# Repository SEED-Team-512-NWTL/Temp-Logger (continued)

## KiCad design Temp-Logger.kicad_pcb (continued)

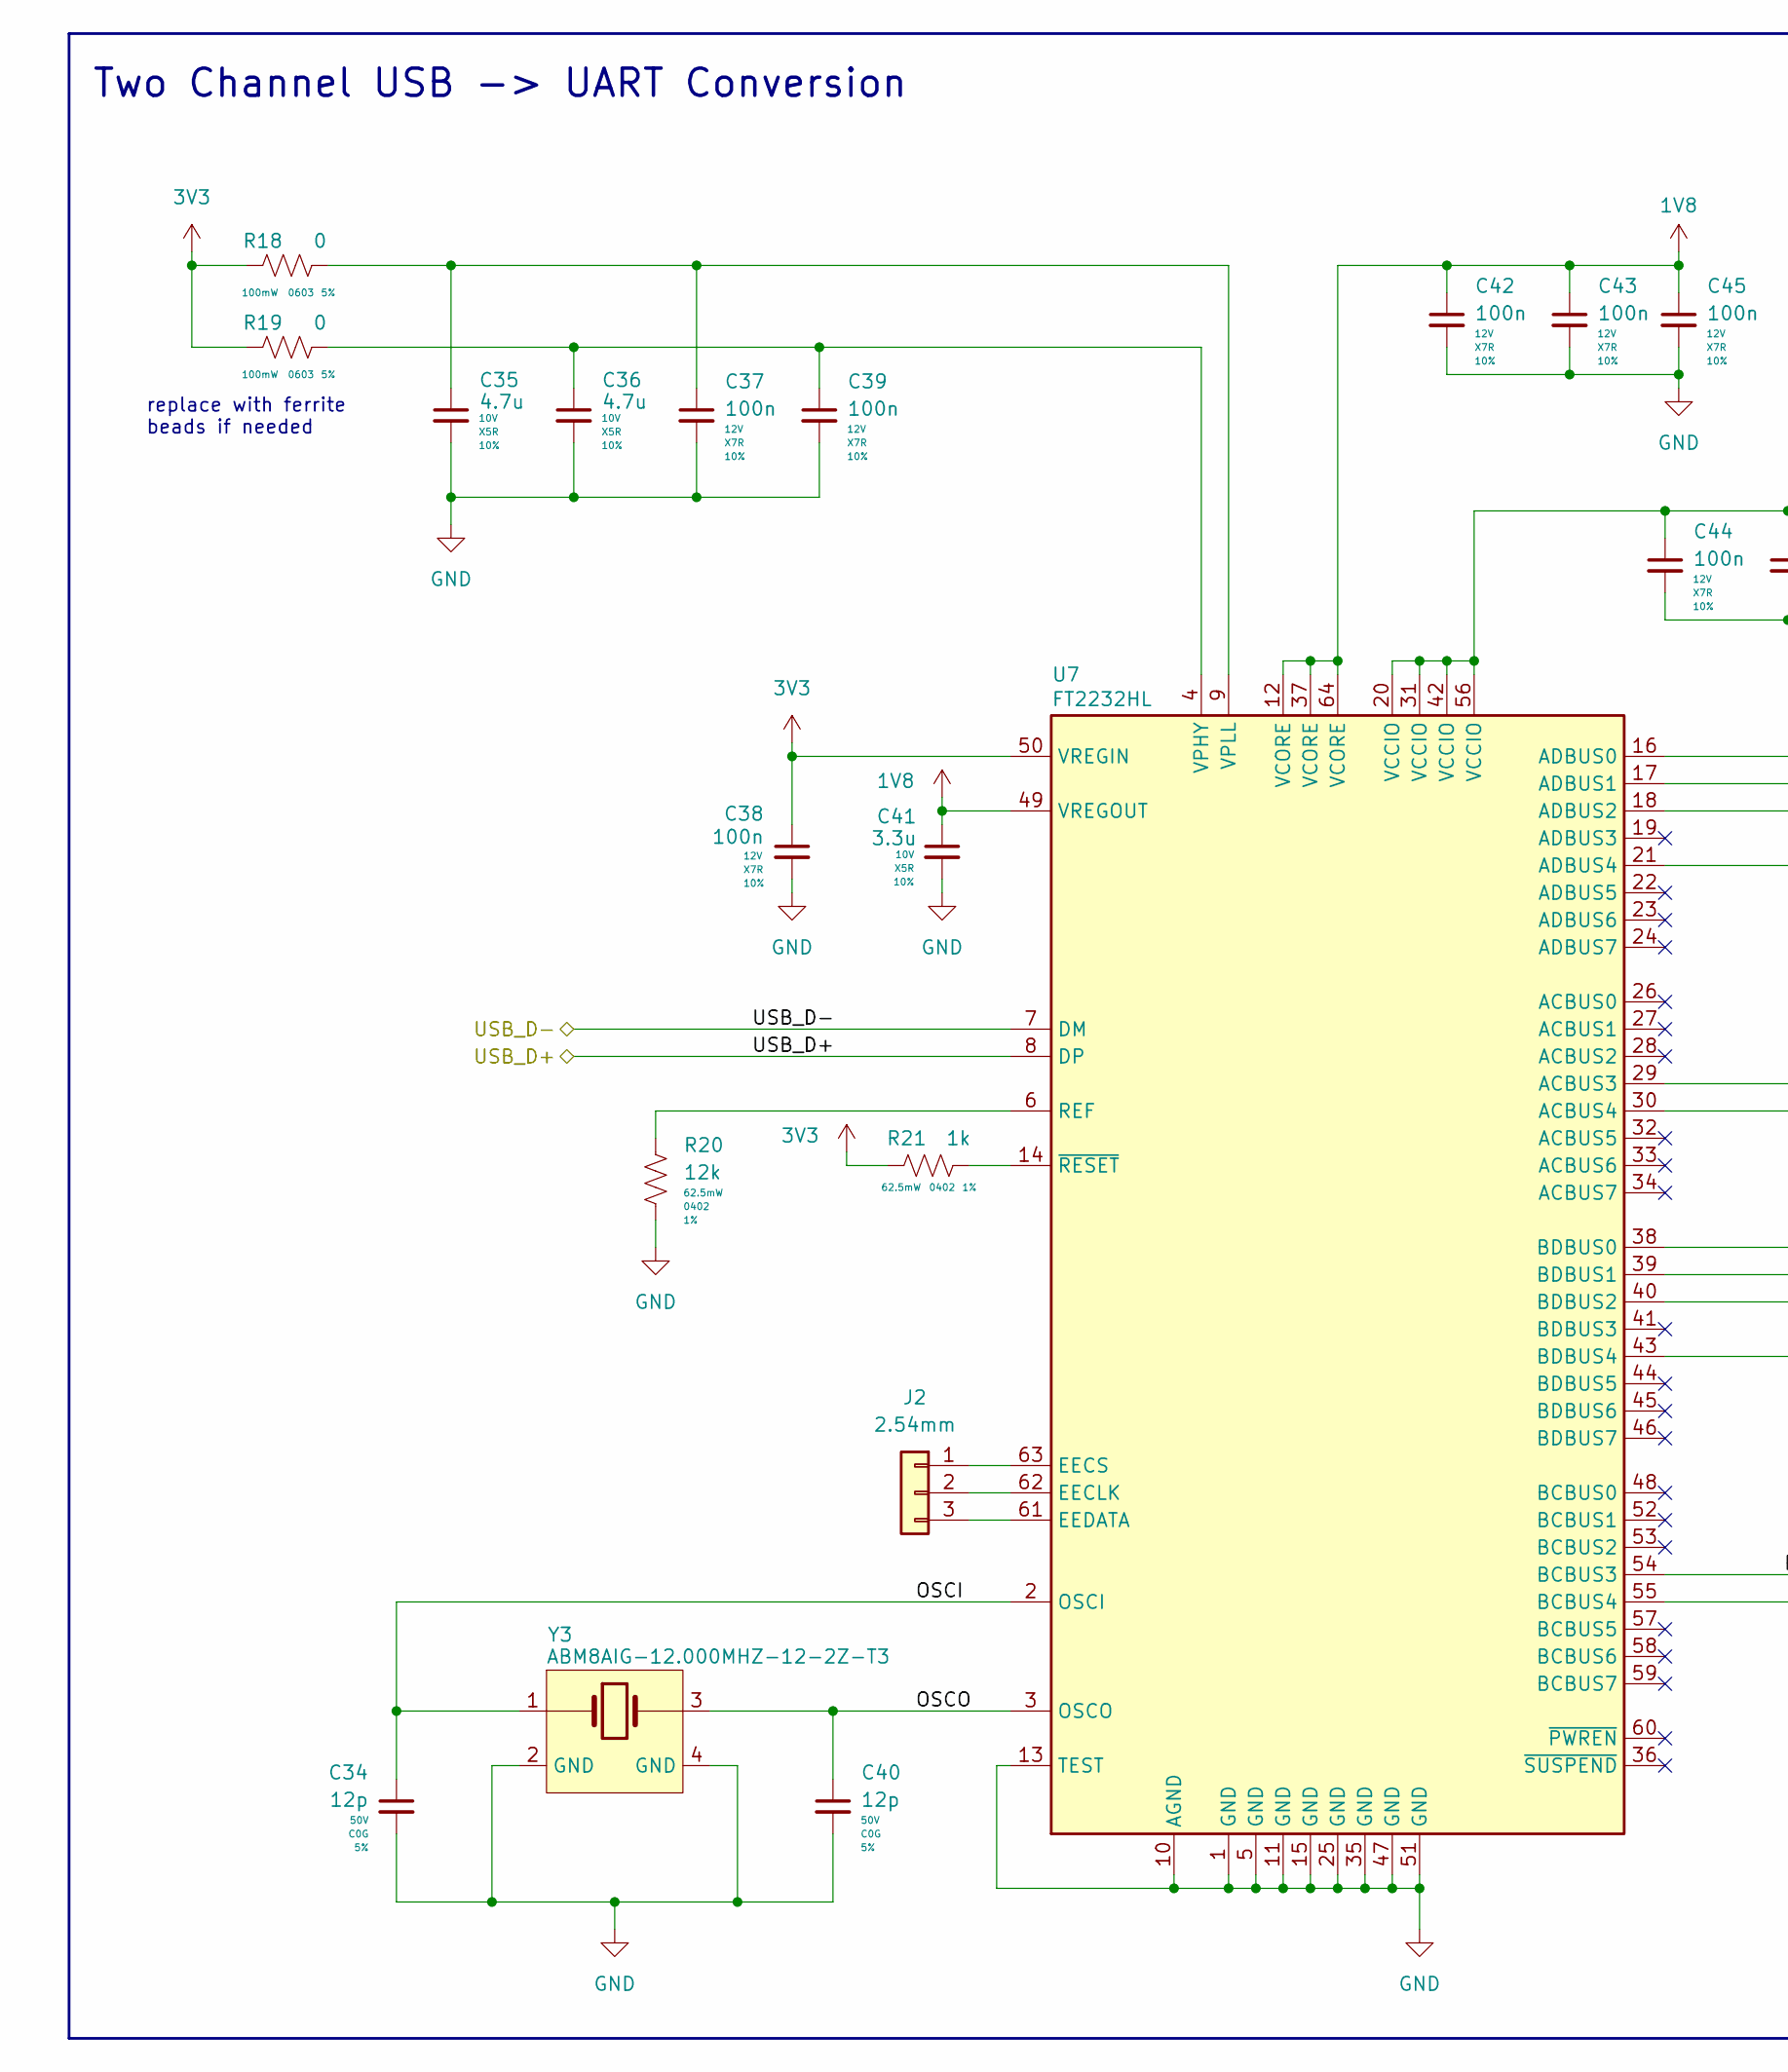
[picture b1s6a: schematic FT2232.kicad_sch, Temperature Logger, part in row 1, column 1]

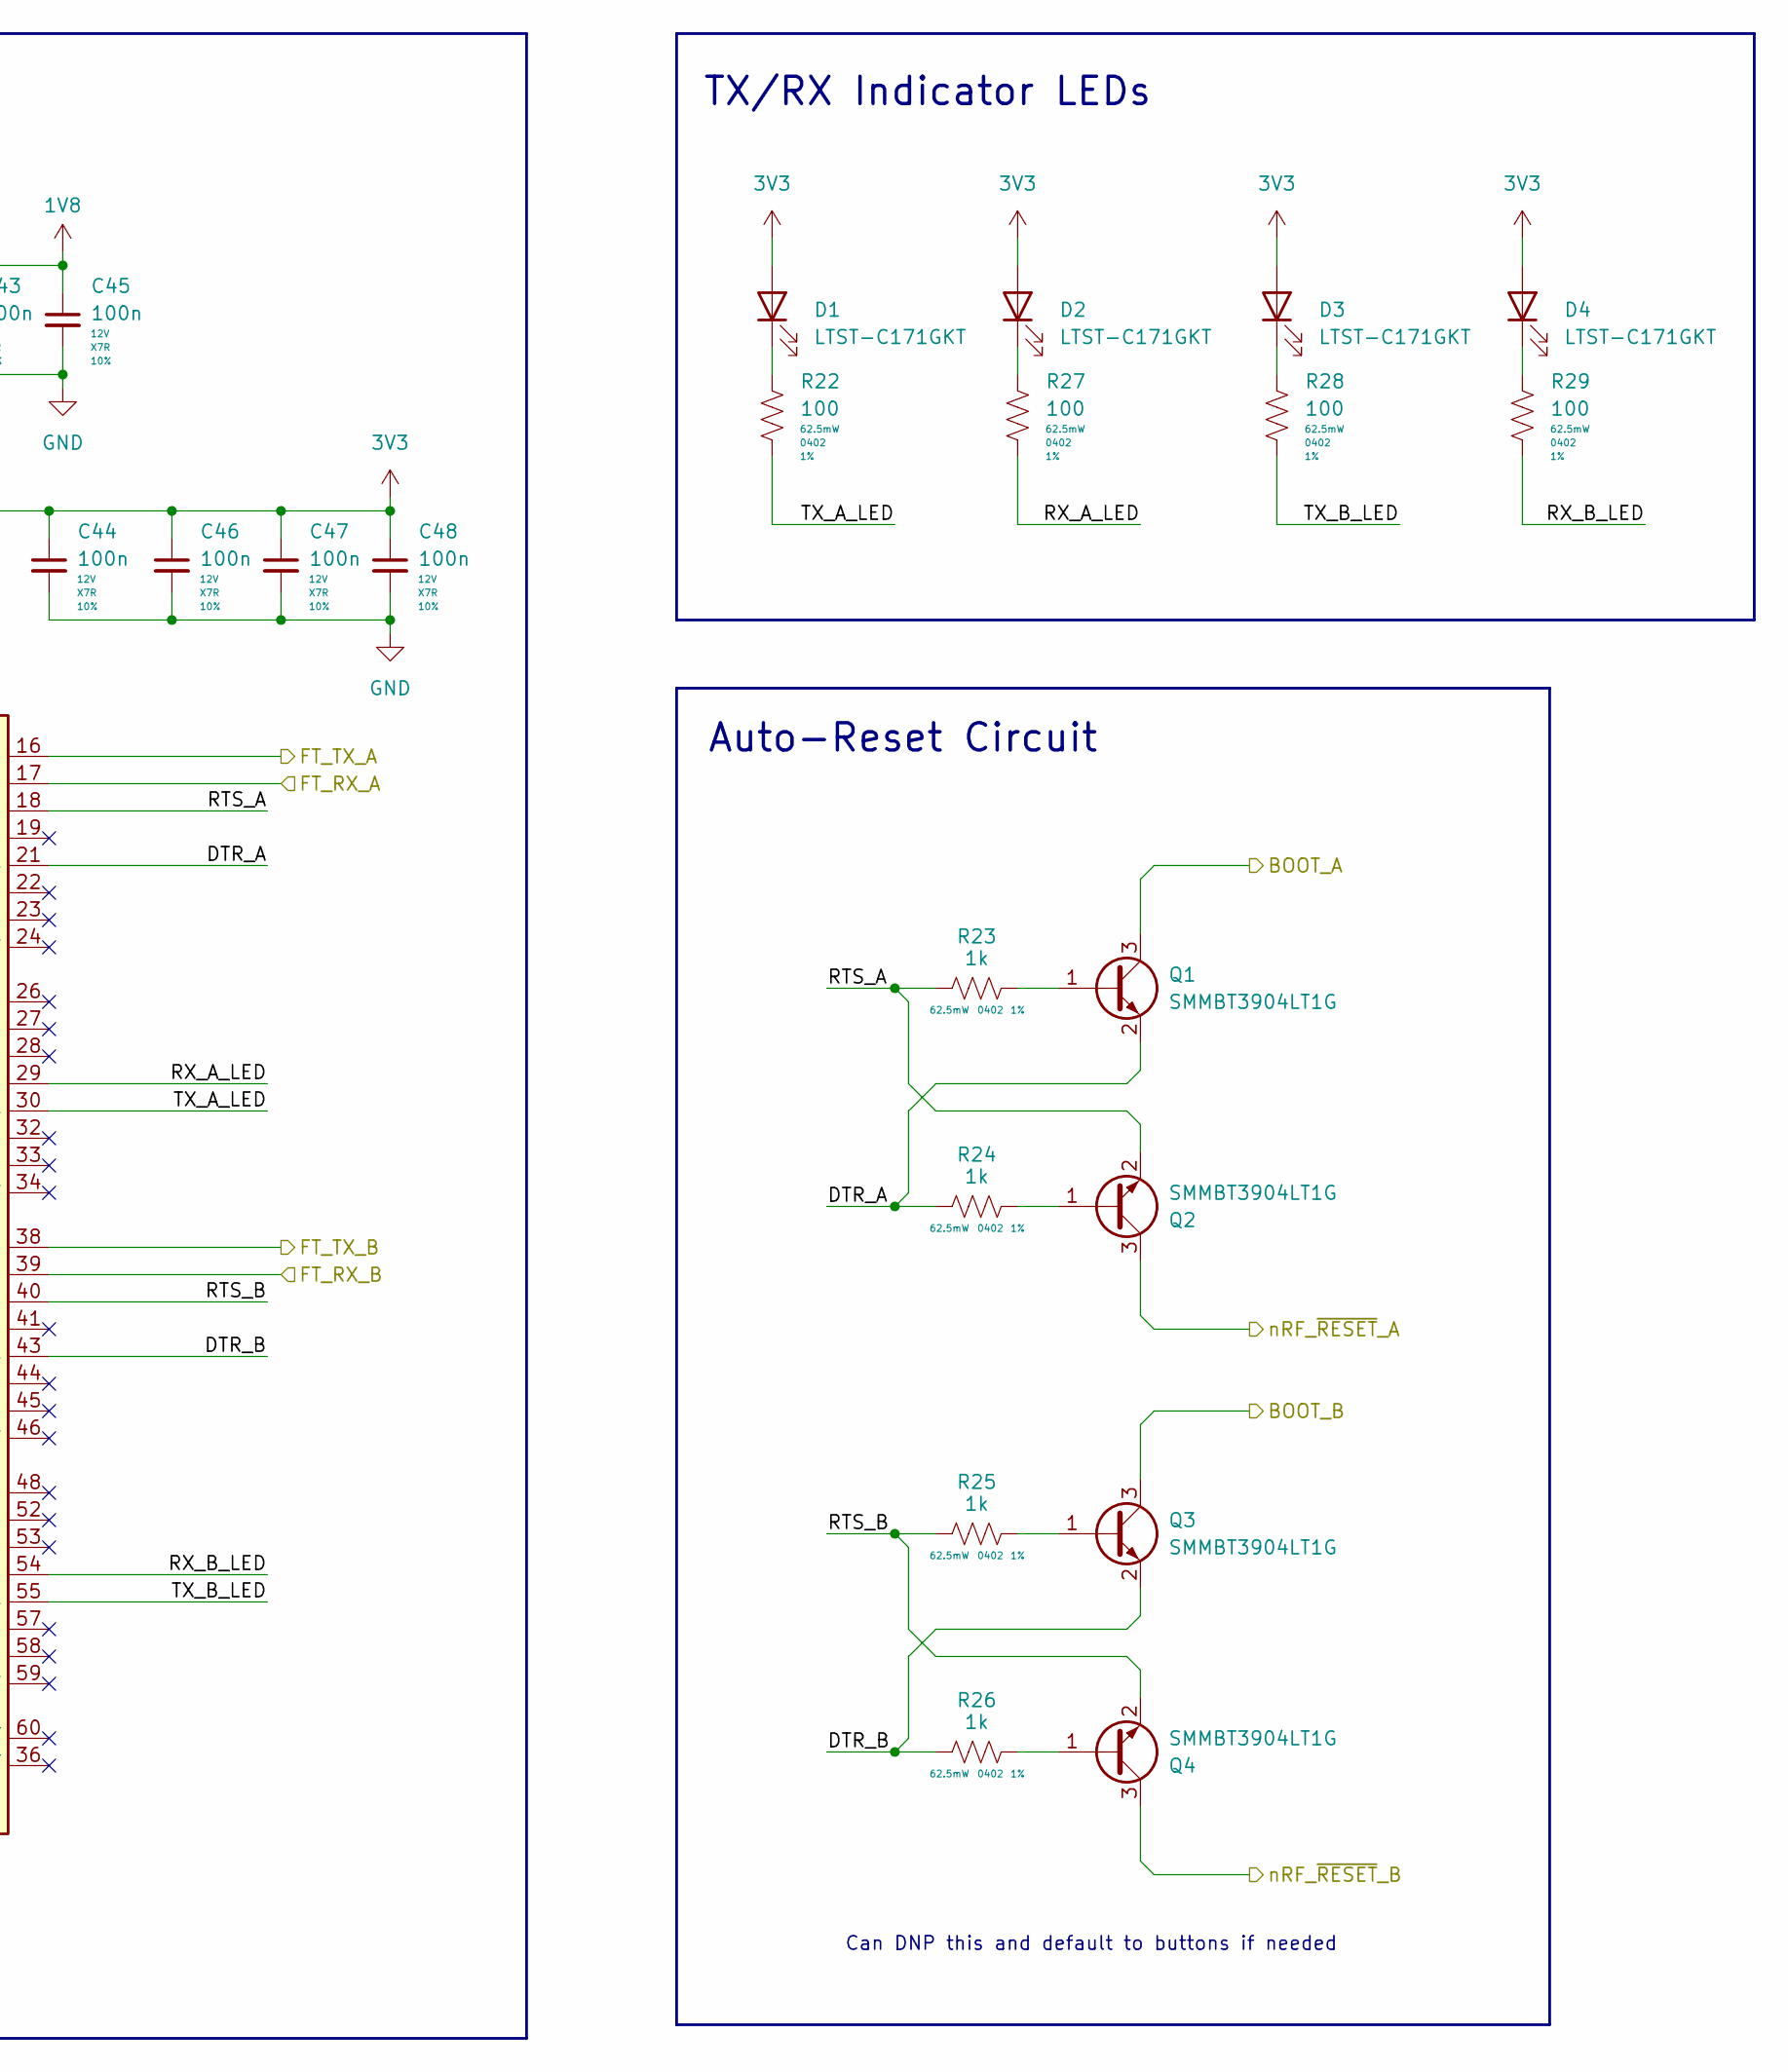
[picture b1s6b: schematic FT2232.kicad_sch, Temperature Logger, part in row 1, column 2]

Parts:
C34, C40: 12p; C_0402_1005Metric_Pad0.74x0.62mm_HandSolder; Voltage Rating 50V; Tolerance 5%; LCSC C85875
C35, C36: 4.7u; C_0603_1608Metric_Pad1.08x0.95mm_HandSolder; Voltage Rating 10V; Tolerance 10%; LCSC C1705
C37, C38, C39, C42, C43, C44, C45, C46, C47, C48: 100n; C_0402_1005Metric_Pad0.74x0.62mm_HandSolder; Voltage Rating 12V; Tolerance 10%; LCSC C1525
C41: 3.3u; C_0603_1608Metric_Pad1.08x0.95mm_HandSolder; Voltage Rating 10V; Tolerance 10%; LCSC C51412
D1, D2, D3, D4: LTST-C171GKT; LED_0805_2012Metric; LCSC C913075
J2: 2.54mm; PinHeader_1x03_P2.54mm_Vertical
Q1, Q2, Q3, Q4: SMMBT3904LT1G; LCSC C84555
R18, R19: 0; R_0603_1608Metric_Pad0.98x0.95mm_HandSolder; Tolerance 5%; LCSC C177335
R20: 12k; R_0402_1005Metric_Pad0.72x0.64mm_HandSolder; Tolerance 1%; LCSC C114760
R21, R23, R24, R25, R26: 1k; R_0402_1005Metric_Pad0.72x0.64mm_HandSolder; Tolerance 1%; LCSC C71623
R22, R27, R28, R29: 100; R_0402_1005Metric_Pad0.72x0.64mm_HandSolder; Tolerance 1%; LCSC C82865
U7: FT2232HL; LQFP-64_10x10mm_P0.5mm; LCSC C27882
Y3: ABM8AIG-12.000MHZ-12-2Z-T3; LCSC C1985448

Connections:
1V8: C41.1, C42.1, C43.1, C45.1, U7.12 (VCORE), U7.37 (VCORE), U7.49 (VREGOUT), U7.64 (VCORE)
3V3: C38.1, C44.1, C46.1, C47.1, C48.1, D1.2 (A), D2.2 (A), D3.2 (A), D4.2 (A), R18.1, R19.1, R21.1, U7.20 (VCCIO), U7.31 (VCCIO), U7.42 (VCCIO), U7.50 (VREGIN), U7.56 (VCCIO); also elsewhere on the board
/Receiver/BOOT_B: Q3.3 (C); also elsewhere on the board
/Receiver/nRF_~RESET_B: Q4.3 (C); also elsewhere on the board
/Transmitter/BOOT_A: Q1.3 (C); also elsewhere on the board
/Transmitter/nRF_~RESET_A: Q2.3 (C); also elsewhere on the board
/USB to UART/FT2232/DTR_A: Q1.2 (E), R24.1, U7.21 (ADBUS4)
/USB to UART/FT2232/DTR_B: Q3.2 (E), R26.1, U7.43 (BDBUS4)
/USB to UART/FT2232/OSCI: C34.1, U7.2 (OSCI), Y3.1
/USB to UART/FT2232/OSCO: C40.1, U7.3 (OSCO), Y3.3
/USB to UART/FT2232/RTS_A: Q2.2 (E), R23.1, U7.18 (ADBUS2)
/USB to UART/FT2232/RTS_B: Q4.2 (E), R25.1, U7.40 (BDBUS2)
/USB to UART/FT2232/RX_A_LED: R27.2, U7.29 (ACBUS3)
/USB to UART/FT2232/RX_B_LED: R29.2, U7.54 (BCBUS3)
/USB to UART/FT2232/TX_A_LED: R22.2, U7.30 (ACBUS4)
/USB to UART/FT2232/TX_B_LED: R28.2, U7.55 (BCBUS4)
/USB to UART/FT2232/USB_D+: U7.8 (DP); also elsewhere on the board
/USB to UART/FT2232/USB_D-: U7.7 (DM); also elsewhere on the board
/USB to UART/FT_RX_A: U7.17 (ADBUS1); also elsewhere on the board
/USB to UART/FT_RX_B: U7.39 (BDBUS1); also elsewhere on the board
/USB to UART/FT_TX_A: U7.16 (ADBUS0); also elsewhere on the board
/USB to UART/FT_TX_B: U7.38 (BDBUS0); also elsewhere on the board
GND: C34.2, C35.2, C36.2, C37.2, C38.2, C39.2, C40.2, C41.2, C42.2, C43.2, C44.2, C45.2, C46.2, C47.2, C48.2, R20.2, U7.1 (GND), U7.5 (GND), U7.10 (AGND), U7.11 (GND), U7.13 (TEST), U7.15 (GND), U7.25 (GND), U7.35 (GND), U7.47 (GND), U7.51 (GND), Y3.2 (GND), Y3.4 (GND); also elsewhere on the board
unnamed: D1.1 (K), R22.1
unnamed: D2.1 (K), R27.1
unnamed: D3.1 (K), R28.1
unnamed: D4.1 (K), R29.1
unnamed: J2.1, U7.63 (EECS)
unnamed: J2.2, U7.62 (EECLK)
unnamed: J2.3, U7.61 (EEDATA)
unnamed: Q1.1 (B), R23.2
unnamed: Q2.1 (B), R24.2
unnamed: Q3.1 (B), R25.2
unnamed: Q4.1 (B), R26.2
unnamed: R20.1, U7.6 (REF)
unnamed: C36.1, C39.1, R19.2, U7.4 (VPHY)
unnamed: C35.1, C37.1, R18.2, U7.9 (VPLL)
unnamed: R21.2, U7.14 (~RESET)

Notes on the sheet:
Auto-Reset Circuit
replace with ferrite beads if needed
TX/RX Indicator LEDs
Two Channel USB -> UART Conversion
Can DNP this and default to buttons if needed

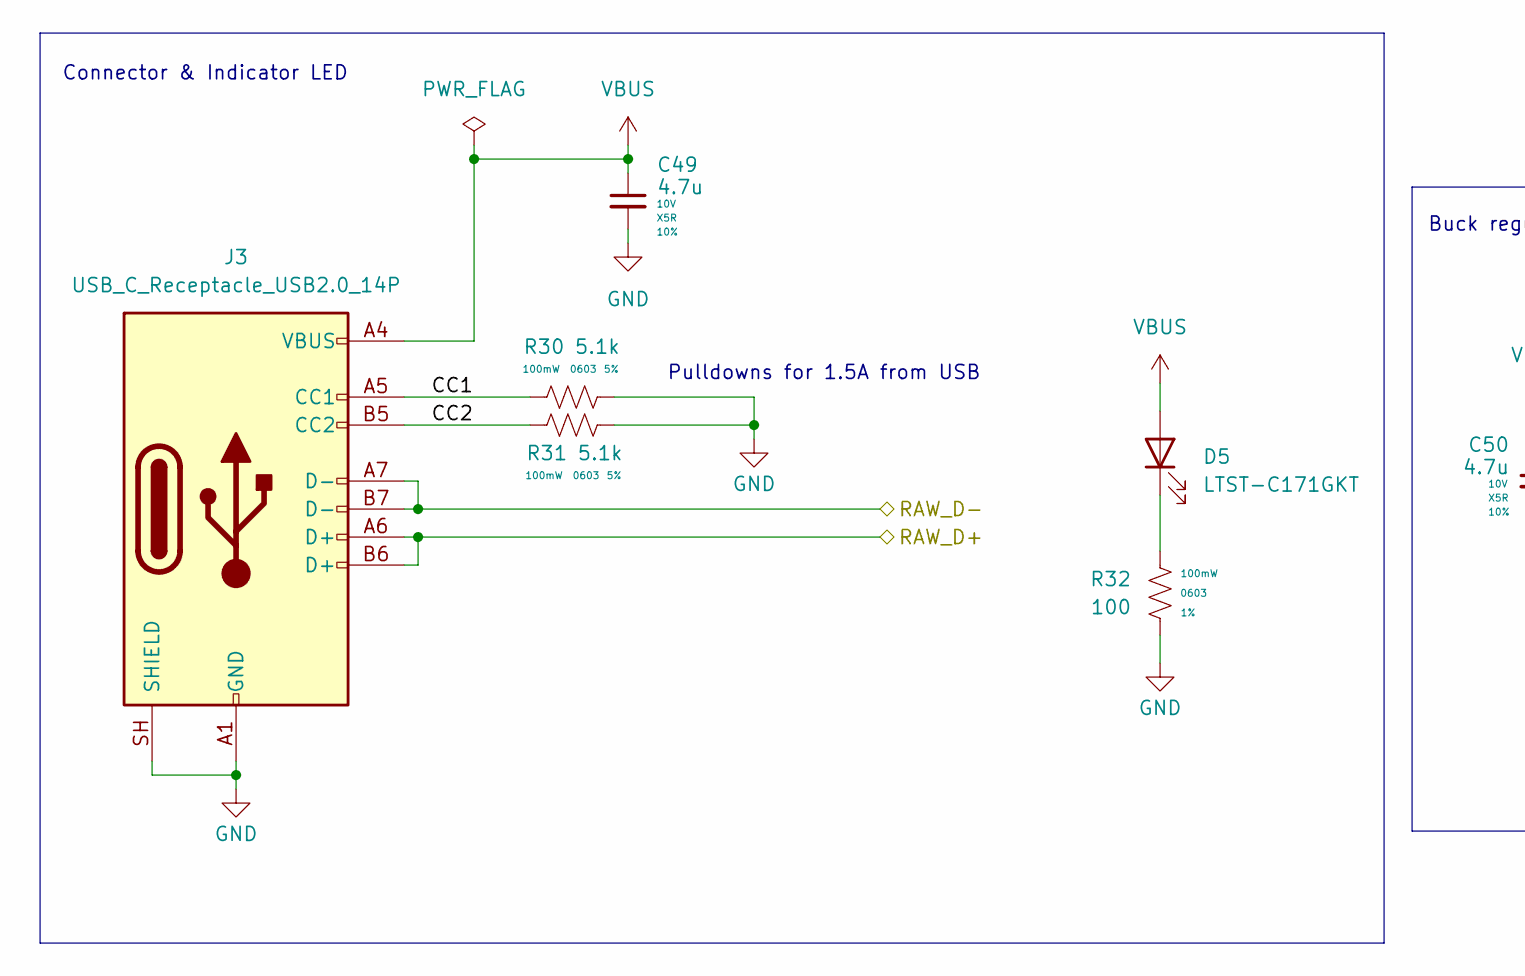
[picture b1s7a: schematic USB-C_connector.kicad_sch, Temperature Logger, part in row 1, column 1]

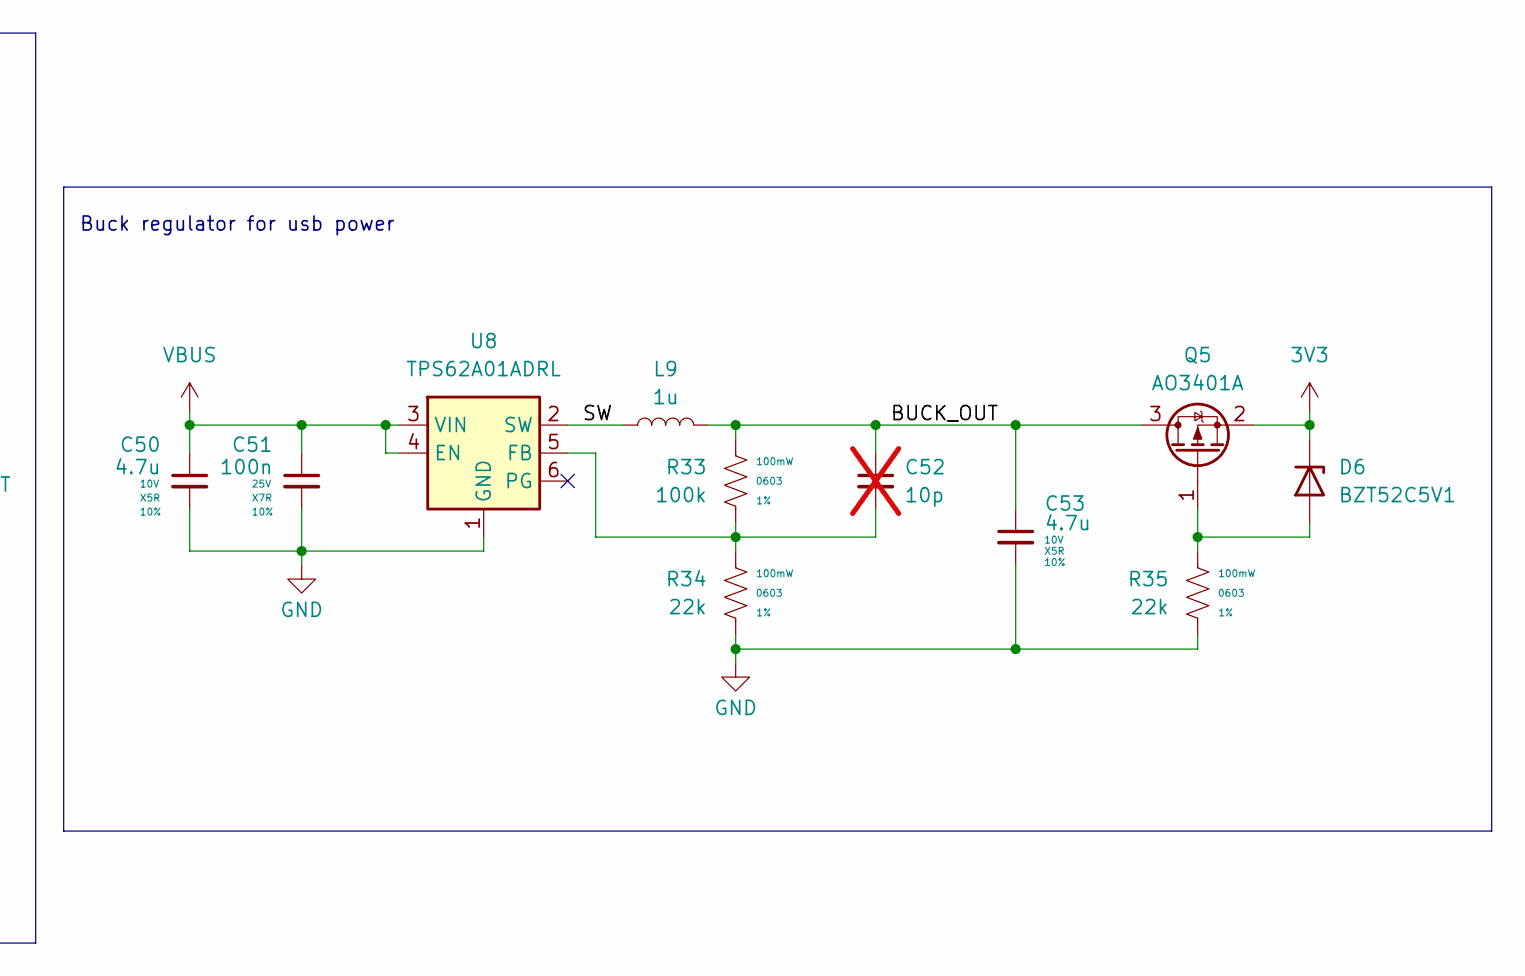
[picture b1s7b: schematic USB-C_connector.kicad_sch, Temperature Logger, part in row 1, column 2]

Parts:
C49, C50: 4.7u; C_0603_1608Metric_Pad1.08x0.95mm_HandSolder; Voltage Rating 10V; Tolerance 10%; LCSC C1705
C51: 100n; C_0603_1608Metric_Pad1.08x0.95mm_HandSolder; Voltage Rating 25V; Tolerance 10%; LCSC C1590
C52: 10p; C_0603_1608Metric; not fitted
C53: 4.7u; C_0603_1608Metric; Voltage Rating 10V; Tolerance 10%; LCSC C1705
D5: LTST-C171GKT; LED_0805_2012Metric; LCSC C913075
D6: BZT52C5V1; D_SOD-123; LCSC C2117
J3: USB_C_Receptacle_USB2.0_14P; USB_C_Receptacle_GCT_USB4105-xx-A_16P_TopMnt_Horizontal; LCSC C3020560
L9: 1u; L_1008_2520Metric_Pad1.43x2.20mm_HandSolder; LCSC C435392
Q5: AO3401A; SOT-23; LCSC C15127
R30, R31: 5.1k; R_0603_1608Metric_Pad0.98x0.95mm_HandSolder; Tolerance 5%; LCSC C14677
R32: 100; R_0603_1608Metric_Pad0.98x0.95mm_HandSolder; Tolerance 1%; LCSC C105588
R33: 100k; R_0603_1608Metric_Pad0.98x0.95mm_HandSolder; Tolerance 1%; LCSC C14675
R34, R35: 22k; R_0603_1608Metric_Pad0.98x0.95mm_HandSolder; Tolerance 1%; LCSC C114065
U8: TPS62A01ADRL; SOT-563; LCSC C5181455

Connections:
3V3: D6.1 (K), Q5.2 (S); also elsewhere on the board
/USB to UART/USB Receptical/BUCK_OUT: C52.1, C53.1, L9.2, Q5.3 (D), R33.2
/USB to UART/USB Receptical/CC1: J3.A5 (CC1), R30.1
/USB to UART/USB Receptical/CC2: J3.B5 (CC2), R31.1
/USB to UART/USB Receptical/RAW_D+: J3.A6 (D+), J3.B6 (D+); also elsewhere on the board
/USB to UART/USB Receptical/RAW_D-: J3.A7 (D-), J3.B7 (D-); also elsewhere on the board
/USB to UART/USB Receptical/SW: L9.1, U8.2 (SW)
GND: C49.2, C50.2, C51.2, C53.2, J3.A1 (GND), J3.A12 (GND), J3.B1 (GND), J3.B12 (GND), J3.SH (SHIELD), R30.2, R31.2, R32.1, R34.1, R35.1, U8.1 (GND); also elsewhere on the board
unnamed: D5.1 (K), R32.2
unnamed: D6.2 (A), Q5.1 (G), R35.2
unnamed: C52.2, R33.1, R34.2, U8.5 (FB)
VBUS: C49.1, C50.1, C51.1, D5.2 (A), J3.A4 (VBUS), J3.A9 (VBUS), J3.B4 (VBUS), J3.B9 (VBUS), U8.3 (VIN), U8.4 (EN); also elsewhere on the board

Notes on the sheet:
Connector & Indicator LED
Buck regulator for usb power
Pulldowns for 1.5A from USB

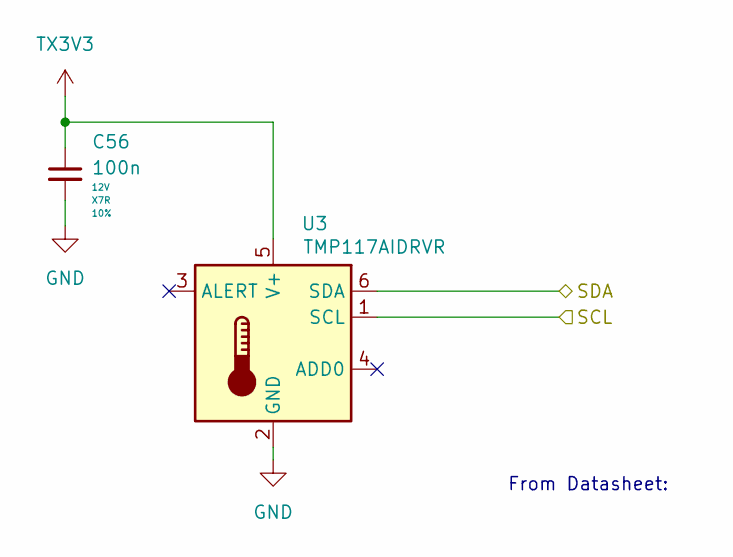
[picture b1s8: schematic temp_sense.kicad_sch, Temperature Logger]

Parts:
C56: 100n; C_0402_1005Metric_Pad0.74x0.62mm_HandSolder; Voltage Rating 12V; Tolerance 10%; LCSC C1525
U3: TMP117AIDRVR; WSON-6-1EP_2x2mm_P0.65mm_EP1x1.6mm; LCSC C699536

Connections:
/Transmitter/TX Microcontroller/SCL: U3.1 (SCL); also elsewhere on the board
/Transmitter/TX Microcontroller/SDA: U3.6 (SDA); also elsewhere on the board
GND: C56.2, U3.2 (GND); also elsewhere on the board
TX3V3: C56.1, U3.5 (V+); also elsewhere on the board

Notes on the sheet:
From Datasheet:

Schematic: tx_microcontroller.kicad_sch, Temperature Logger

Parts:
C1, C6: 2.2u; C_0201_0603Metric; Voltage Rating 6.3V; Tolerance 20%; LCSC C76933
C2: 10u; C_0402_1005Metric_Pad0.74x0.62mm_HandSolder; Voltage Rating 12V; Tolerance 20%; LCSC C15525
C3: 100n; C_0201_0603Metric; Voltage Rating 6.3V; Tolerance 20%; LCSC C284992
C4: 10n; C_0201_0603Metric; Voltage Rating 12V; Tolerance 10%; LCSC C309453
C5: 2.2n; C_0201_0603Metric; Voltage Rating 6.3V; Tolerance 10%; LCSC C526947
C8: 3.9p; C_0201_0603Metric; Voltage Rating 50V; Tolerance ±0.25pF; LCSC C76926
C9: 1.5p; C_0201_0603Metric; Part Number GJM0335C1E1R5WB01; LCSC C435397
C10, C11, C14: 100n; C_0201_0603Metric; Voltage Rating 6.3V; Tolerance 20%; LCSC Part # C284992
C12: 2.0p; C_0201_0603Metric; Part Number GJM0335C1E2R0WB01; LCSC C668326
C15: 0.3p; C_0201_0603Metric; LCSC C76927
D9: LTST-C171GKT; LED_0805_2012Metric; LCSC C913075
J8: MM8130-2600RA2; LCSC C167503
J10: 1mm; PinHeader_1x02_P1.00mm_Vertical; not fitted
L1: 4.7u; L_0603_1608Metric; LCSC C76799
L2: 2.7n; L_0201_0603Metric; Part Number GJM0335C1E1R5WB01; LCSC C7216765
L3, L4: 3.5n; L_0201_0603Metric; Part Number LQP03HQ3N5B02; LCSC C3911055
Q7: SMMBT3904LT1G; LCSC C84555
R5: 0; R_0201_0603Metric; Tolerance 5%; LCSC C100147
R6: 330m; R_1206_3216Metric_Pad1.30x1.75mm_HandSolder; Tolerance 1%; LCSC C2932844
R7: 1k; R_0201_0603Metric; Tolerance 5%; LCSC C131396
R10, R11: 0; R_0603_1608Metric_Pad0.98x0.95mm_HandSolder; Tolerance 5%; LCSC C177335
R39, R40: 4.7k; R_0402_1005Metric_Pad0.72x0.64mm_HandSolder; Tolerance 5%; LCSC C105870
R43: 100; R_0402_1005Metric_Pad0.72x0.64mm_HandSolder; Tolerance 1%; LCSC C82865
SW1: KMR211G LFS; SW_Push_1P1T_NO_CK_KMR2; LCSC C221675
TP1, TP2, TP3, TP4, TP5, TP6, TP7, TP9, TP10, TP11: 1.0mm; TestPoint_Pad_D1.0mm
U1: nRF54L15-QFAA-R; NRF54L15-QFAA-R
Y1: ECS-320-8-37B-CKY-TR; LCSC C2636238
Y5: SC-20S,32.768kHz,20PPM,9pF; LCSC C97603

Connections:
3V3: R6.1, TP2.1 (1_1); also elsewhere on the board
/Transmitter/BOOT_A: U1.24 (P0.01); also elsewhere on the board
/Transmitter/Piezoelectric/PWM+: R10.1, U1.6 (P1.05/AIN1/TAMPC); also elsewhere on the board
/Transmitter/Piezoelectric/PWM-: R11.1, U1.7 (P1.06/AIN2/TAMPC); also elsewhere on the board
/Transmitter/TX Microcontroller/ANT: J8.2 (OUT)
/Transmitter/TX Microcontroller/LED: Q7.1 (B), U1.20 (P2.09/TRACEDATA[2]/SPI.SDI/SDO)
/Transmitter/TX Microcontroller/RF: C15.1, J8.1 (IN), L4.2
/Transmitter/TX Microcontroller/SCL: R40.2, U1.37 (P1.09/TAMPC); also elsewhere on the board
/Transmitter/TX Microcontroller/SDA: R39.2, U1.38 (P1.10/TAMPC); also elsewhere on the board
/Transmitter/TX Microcontroller/SWDCLK: J10.1, TP9.1 (1_1), U1.26 (SWDCLK)
/Transmitter/TX Microcontroller/SWDIO: J10.2, TP10.1 (1_1), U1.25 (SWDIO)
/Transmitter/TX Microcontroller/~RESET: C8.1, R7.1, TP7.1 (1_1), U1.30 (~RESET)
/Transmitter/nRF_URXD_A: U1.18 (P2.07/TRACEDATA[0]/SWO/SPI.DCX); also elsewhere on the board
/Transmitter/nRF_UTXD_A: U1.19 (P2.08/TRACEDATA[1]/SPI.SDI/SDO); also elsewhere on the board
/Transmitter/nRF_~RESET_A: R7.2, SW1.2; also elsewhere on the board
GND: C1.2, C2.2, C3.2, C4.2, C5.2, C6.2, C8.2, C9.2, C10.2, C11.2, C12.2, C14.2, C15.2, J8.3 (GND), J8.4 (GND), J8.5 (GND), J8.6 (GND), Q7.2 (E), SW1.1, TP11.1 (1_1), U1.32 (VSS_PA), U1.44 (VSS), U1.49 (VSS), Y1.2 (GND), Y1.4 (GND); also elsewhere on the board
unnamed: C9.1, L2.2, L3.1
unnamed: C12.1, L3.2, L4.1
unnamed: D9.1 (K), R43.1
unnamed: Q7.3 (C), R43.2
unnamed: L2.1, U1.31 (ANT)
unnamed: L1.2, TP3.1 (1_1), U1.46 (DCC)
unnamed: C1.1, C4.1, C5.1, R5.1, TP4.1 (1_1), U1.33 (DECRF), U1.43 (DECA)
unnamed: C6.1, L1.1, R5.2, TP1.1 (1_1), U1.45 (DECD)
unnamed: U1.34 (XC1), Y1.3
unnamed: U1.35 (XC2), Y1.1
unnamed: U1.1 (P1.00/XL1), Y5.2
unnamed: U1.2 (P1.01/XL2), Y5.1
unnamed: R10.2, U1.5 (P1.04/AIN0/TAMPC)
unnamed: R11.2, U1.8 (P1.07/AIN3/TAMPC)
TX3V3: C2.1, C3.1, C10.1, C11.1, C14.1, D9.2 (A), R6.2, R39.1, R40.1, TP5.1 (1_1), TP6.1 (1_1), U1.10 (VDD), U1.22 (VDD), U1.36 (VDD), U1.47 (VDD), U1.48 (VDD); also elsewhere on the board

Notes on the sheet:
SEE DATASHEET FOR GND ROUTING
Resistor and test points for measuring current draw
Replace w/ FB if needed
~{RESET} pulled up internally

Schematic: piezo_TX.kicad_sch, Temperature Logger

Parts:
C17, C18: 1u; C_0603_1608Metric_Pad1.08x0.95mm_HandSolder; Voltage Rating 50V; Tolerance x%; not fitted
J1: 1053091102; LCSC C2938824
R12, R13: 0; R_0603_1608Metric_Pad0.98x0.95mm_HandSolder; Tolerance 5%; LCSC C177335

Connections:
/Transmitter/Piezoelectric/PWM+: R12.1; also elsewhere on the board
/Transmitter/Piezoelectric/PWM-: R13.1; also elsewhere on the board
GND: C17.2, C18.2; also elsewhere on the board
unnamed: C17.1, J1.2, R12.2
unnamed: C18.1, J1.1, R13.2

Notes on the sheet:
Optional filters

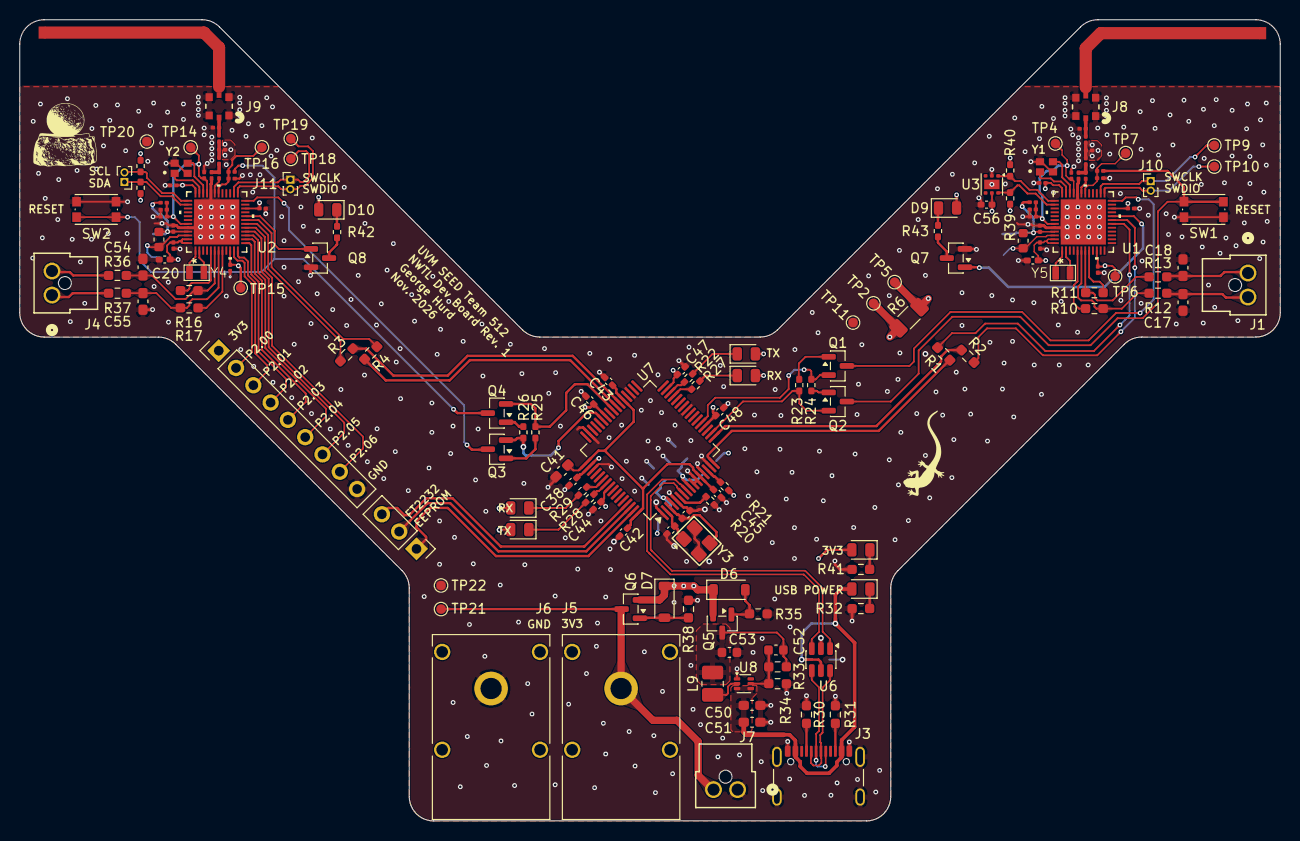
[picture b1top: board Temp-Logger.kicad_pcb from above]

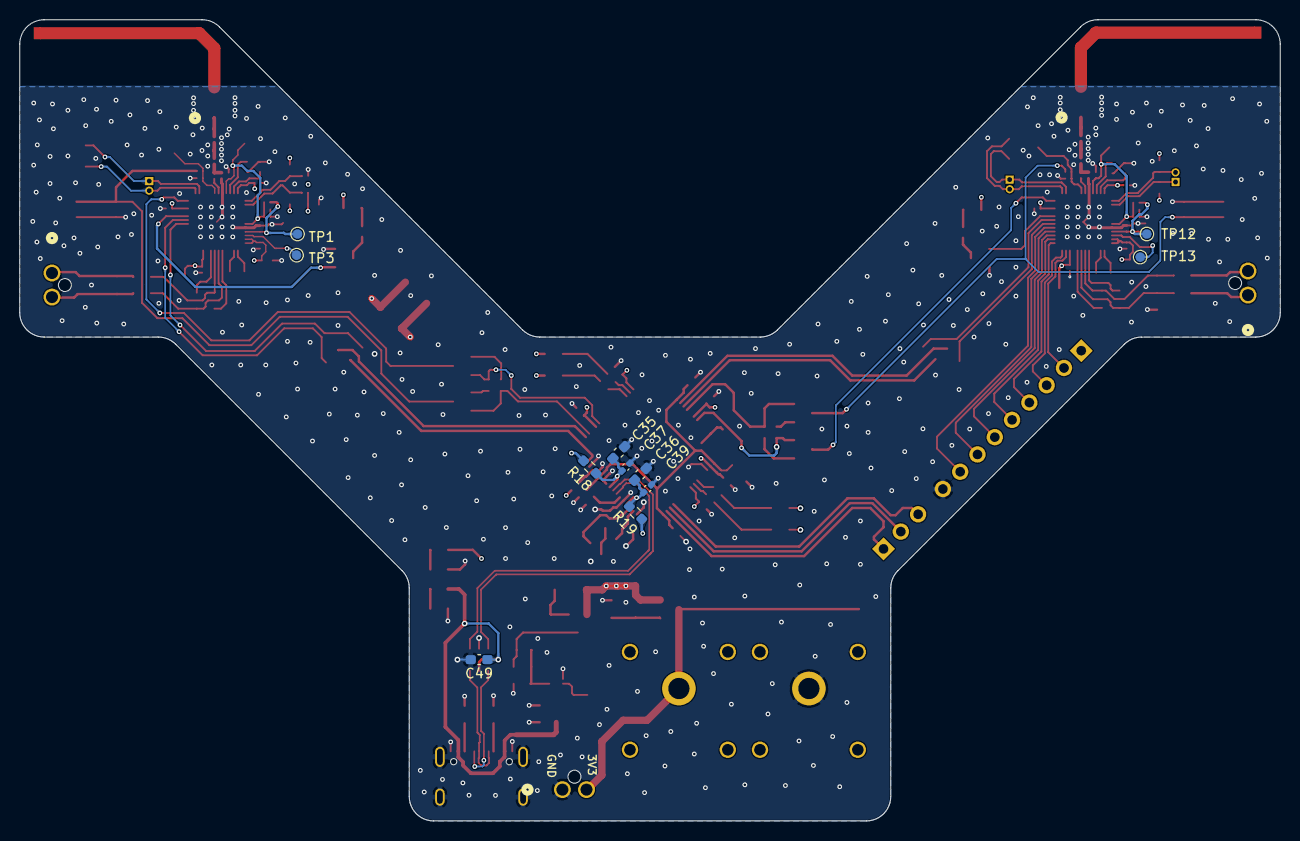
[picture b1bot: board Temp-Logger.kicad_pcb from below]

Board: 4 copper layers, 130.9 x 83.2 mm, 167 parts (11 on the bottom side), 113 nets.

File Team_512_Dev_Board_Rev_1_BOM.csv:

"Id";"Designator";"Footprint";"Quantity";"Designation";"Supplier and ref";
1;"C1, C6, C19, C24";"C_0201_0603Metric";4;"2.2u";;;
2;"C2, C20";"C_0402_1005Metric_Pad0.74x0.62mm_HandSolder";2;"10u";;;
3;"C3, C10, C11, C14, C21, C28, C29, C32";"C_0201_0603Metric";8;"100n";;;
4;"C4, C22";"C_0201_0603Metric";2;"10n";;;
5;"C5, C23";"C_0201_0603Metric";2;"2.2n";;;
6;"C8, C26";"C_0201_0603Metric";2;"3.9p";;;
7;"C9, C27";"C_0201_0603Metric";2;"1.5p";;;
8;"C12, C30";"C_0201_0603Metric";2;"2.0p";;;
9;"C15, C33";"C_0201_0603Metric";2;"0.3p";;;
10;"C17, C18, C54, C55";"C_0603_1608Metric_Pad1.08x0.95mm_HandSolder";4;"1u";;;
11;"C34, C40";"C_0402_1005Metric_Pad0.74x0.62mm_HandSolder";2;"12p";;;
12;"C35, C36, C49, C50";"C_0603_1608Metric_Pad1.08x0.95mm_HandSolder";4;"4.7u";;;
13;"C37, C38, C39, C42, C43, C44, C45, C46, C47, C48, C56";"C_0402_1005Metric_Pad0.74x0.62mm_HandSolder";11;"100n";;;
14;"C41";"C_0603_1608Metric_Pad1.08x0.95mm_HandSolder";1;"3.3u";;;
15;"C51";"C_0603_1608Metric_Pad1.08x0.95mm_HandSolder";1;"100n";;;
16;"C52";"C_0603_1608Metric";1;"10p";;;
17;"C53";"C_0603_1608Metric";1;"4.7u";;;
18;"D1, D2, D3, D4, D5, D8, D9, D10";"LED_0805_2012Metric";8;"LTST-C171GKT";;;
19;"D6, D7";"D_SOD-123";2;"BZT52C5V1";;;
20;"J1, J4, J7";"1053091102";3;"1053091102";;;
21;"J2";"PinHeader_1x03_P2.54mm_Vertical";1;"2.54mm";;;
22;"J3";"USB_C_Receptacle_GCT_USB4105-xx-A_16P_TopMnt_Horizontal";1;"USB_C_Receptacle_USB2.0_14P";;;
23;"J5, J6";"Banana_Cliff_FCR7350B_S16N-PC_Horizontal";2;"FCR7350B";;;
24;"J8, J9";"MM8130-2600RA2";2;"MM8130-2600RA2";;;
25;"J10, J11, J12";"PinHeader_1x02_P1.00mm_Vertical";3;"1mm";;;
26;"L1, L5";"L_0603_1608Metric";2;"4.7u";;;
27;"L2, L6";"L_0201_0603Metric";2;"2.7n";;;
28;"L3, L4, L7, L8";"L_0201_0603Metric";4;"3.5n";;;
29;"L9";"L_1008_2520Metric_Pad1.43x2.20mm_HandSolder";1;"1u";;;
30;"Q1, Q2, Q3, Q4, Q7, Q8";"SMMBT3904LT1G";6;"SMMBT3904LT1G";;;
31;"Q5, Q6";"SOT-23";2;"AO3401A";;;
32;"R1, R2, R3, R4, R10, R11, R12, R13, R16, R17, R18, R19, R36, R37";"R_0603_1608Metric_Pad0.98x0.95mm_HandSolder";14;"0";;;
33;"R5, R14";"R_0201_0603Metric";2;"0";;;
34;"R6";"R_1206_3216Metric_Pad1.30x1.75mm_HandSolder";1;"100m";;;
35;"R7, R15";"R_0201_0603Metric";2;"1k";;;
36;"R20";"R_0402_1005Metric_Pad0.72x0.64mm_HandSolder";1;"12k";;;
37;"R21, R23, R24, R25, R26";"R_0402_1005Metric_Pad0.72x0.64mm_HandSolder";5;"1k";;;
38;"R22, R27, R28, R29";"R_0402_1005Metric_Pad0.72x0.64mm_HandSolder";4;"100";;;
39;"R30, R31";"R_0603_1608Metric_Pad0.98x0.95mm_HandSolder";2;"5.1k";;;
40;"R32, R41, R42, R43";"R_0603_1608Metric_Pad0.98x0.95mm_HandSolder";4;"100";;;
41;"R33";"R_0603_1608Metric_Pad0.98x0.95mm_HandSolder";1;"100k";;;
42;"R34, R35, R38";"R_0603_1608Metric_Pad0.98x0.95mm_HandSolder";3;"22k";;;
43;"R39, R40";"R_0402_1005Metric_Pad0.72x0.64mm_HandSolder";2;"4.7k";;;
44;"SW1, SW2";"SW_Push_1P1T_NO_CK_KMR2";2;"KMR211G LFS";;;
45;"TP1, TP2, TP3, TP4, TP5, TP6, TP7, TP9, TP10, TP11, TP12, TP13, TP14, TP15, TP16, TP18, TP19, TP20, TP21, TP22";"TestPoint_Pad_D1.0mm";20;"1.0mm";;;
46;"U1, U2";"NRF54L15-QFAA-R";2;"nRF54L15-QFAA-R";;;
47;"U3";"WSON-6-1EP_2x2mm_P0.65mm_EP1x1.6mm";1;"TMP117xxDRV";;;
48;"U6";"SOT-23-6";1;"USBLC6-2SC6";;;
49;"U7";"LQFP-64_10x10mm_P0.5mm";1;"FT2232HL";;;
50;"U8";"SOT-563";1;"TPS62A01ADRL";;;
51;"Y1, Y2";"ECS-320-8-37B-CKY-TR";2;"ECS-320-8-37B-CKY-TR";;;
52;"Y3";"ABM8AIG-12.000MHZ-12-2Z-T3";1;"ABM8AIG-12.000MHZ-12-2Z-T3";;;
53;"Y4, Y5";"SC-20S,32.768kHz,20PPM,9pF";2;"SC-20S,32.768kHz,20PPM,9pF";;;
